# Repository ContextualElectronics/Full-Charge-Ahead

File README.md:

# Full-Charge-Ahead
A battery controller/charger for the Roll With It project

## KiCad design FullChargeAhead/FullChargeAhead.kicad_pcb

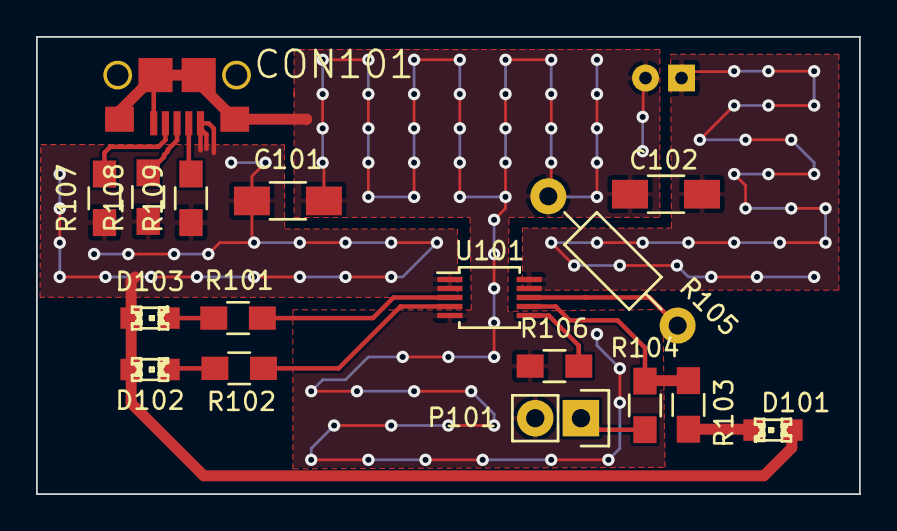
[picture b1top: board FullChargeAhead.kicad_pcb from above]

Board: 2 copper layers, 45.7 x 25.4 mm, 18 parts (1 on the bottom side), 15 nets.

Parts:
C101, C102: 4.7U; C_1206_HandSoldering
CON101: USB-MICRO-B; 10118193
D101: NOPOP; LED-0805
D102, D103: LED; LED-0805
P101: CONN_01X02; Pin_Header_Straight_1x02
P102: CONN_01X02; JST_2pin
R101, R102: 470; R_0805_HandSoldering
R103, R107, R108, R109: NOPOP; R_0805_HandSoldering
R104: 1K; R_0805_HandSoldering
R105: 10K; Resistor_Horizontal_RM10mm
R106: 2K; R_0805_HandSoldering
U101: MCP73834-FCI/UN; MSOP-10_3x3mm_Pitch0.5mm

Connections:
/Vbat: C102.1, P102.1, U101.9, U101.10
/Vdd: C101.1, CON101.1, D101.1, D102.1, D103.1, R107.1, R108.1, R109.1, U101.1, U101.2
GND: C101.2, C102.2, CON101.5, CON101.6, CON101.7, CON101.8, CON101.9, P101.2, P102.2, R105.1, R106.1, U101.5
unnamed: CON101.2, R109.2
unnamed: CON101.3, R108.2
unnamed: CON101.4, R107.2
unnamed: D101.2, R103.2
unnamed: D102.2, R102.2
unnamed: D103.2, R101.2
unnamed: P101.1, R104.2
unnamed: R101.1, U101.3
unnamed: R102.1, U101.4
unnamed: R103.1, R104.1, U101.7
unnamed: R105.2, U101.8
unnamed: R106.2, U101.6

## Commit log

2015-03-13 Adding initial copy of part comparison document to the repository
2015-03-14 Added more parts to the potential list of solutions
2015-03-17 Created schematic and included a .gitignore from the CSOS project
2015-03-17 Did ERC check, annotated and created layout file
2015-03-20 Added new library and imported footprints
2015-03-21 Halfway through layout, top planes poured
2015-03-21 After cloning this project, the passives weren't connected, this is to fix that.
2015-03-21 Added planes and board outline, completed routing traces
2015-03-22 Finished DRC and added title & silkscreen image
2015-03-23 Change to R105 and generated final gerbers
2015-04-14 Updated schematic for MPN and generated BOM
